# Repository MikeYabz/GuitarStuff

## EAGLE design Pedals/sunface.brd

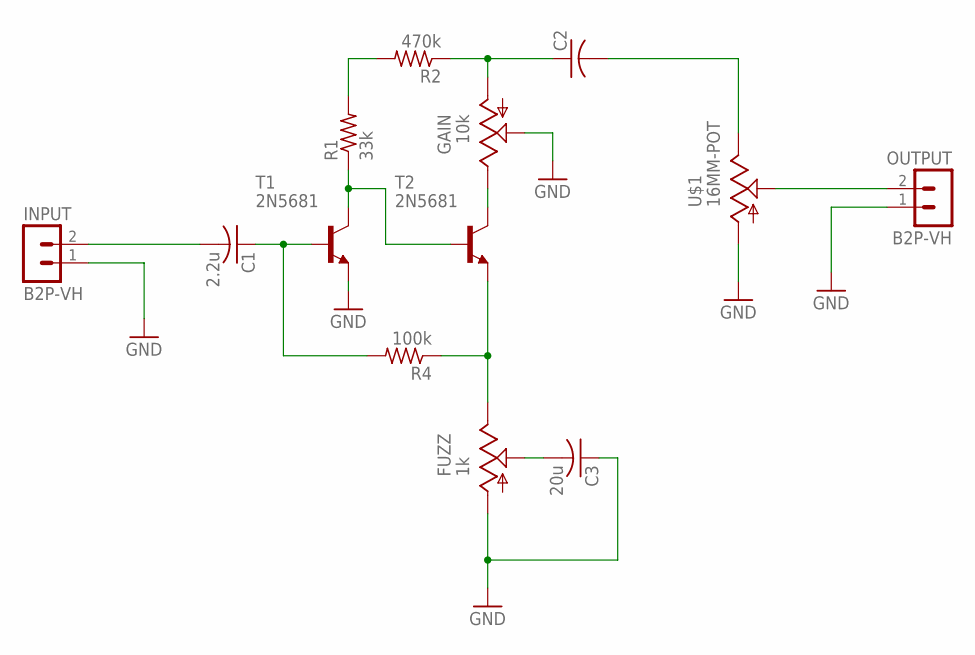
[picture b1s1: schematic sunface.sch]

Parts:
C1: 2.2u; C050-045X075
C2: C-US050-045X075; C050-045X075
C3: 20u; C050-045X075
FUZZ: 1k; ALPHA-16-MINI
GAIN: 10k; ALPHA-16-MINI
INPUT: B2P-VH
OUTPUT: B2P-VH
R1: 33k; 0411/15
R2: 470k; 0411/15
R4: 100k; 0411/15
T1, T2: 2N5681; TO5
U$1: 16MM-POT; ALPHA-16-MINI

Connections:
GND: C3.1, FUZZ.LEFT, GAIN.WIPER, INPUT.1, OUTPUT.1, T1.1 (E), U$1.LEFT
unnamed: R1.1, T1.3 (C), T2.2 (B)
unnamed: C1.1, R4.2, T1.2 (B)
unnamed: R1.2, R2.2
unnamed: C2.1, GAIN.LEFT, R2.1
unnamed: GAIN.RIGHT, T2.3 (C)
unnamed: FUZZ.RIGHT, R4.1, T2.1 (E)
unnamed: C2.2, U$1.RIGHT
unnamed: OUTPUT.2, U$1.WIPER
unnamed: C1.2, INPUT.2
unnamed: C3.2, FUZZ.WIPER

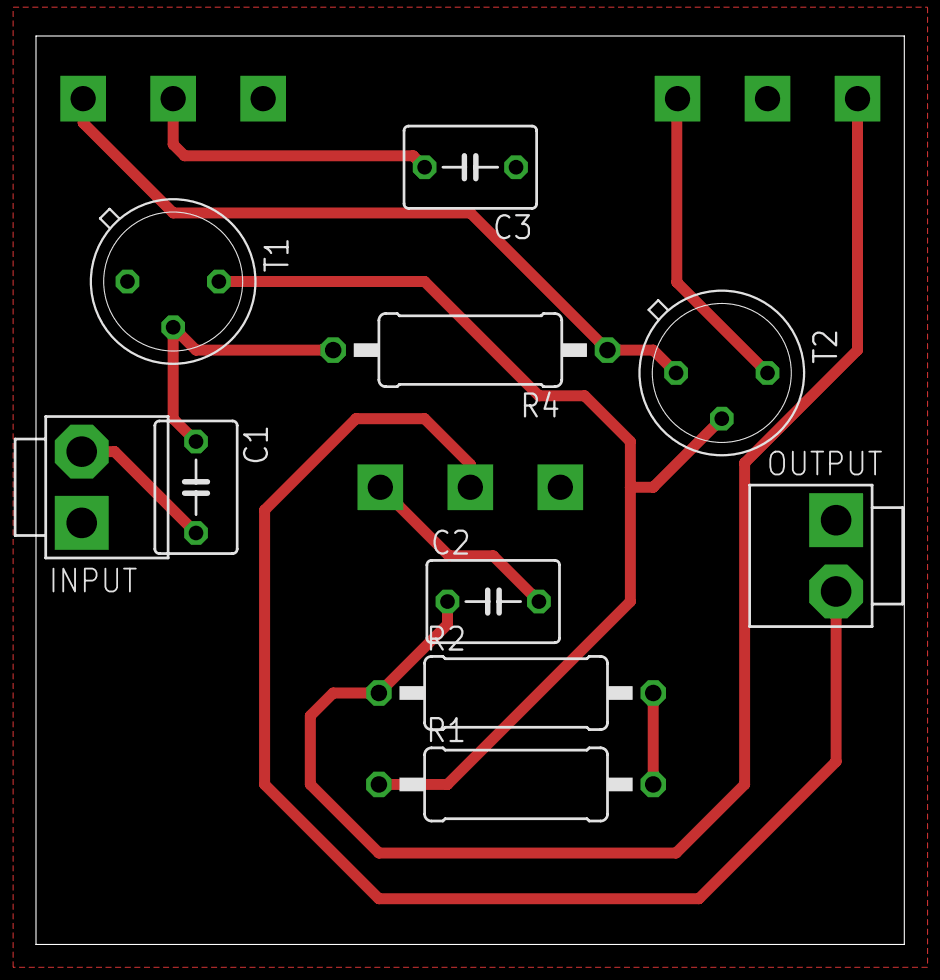
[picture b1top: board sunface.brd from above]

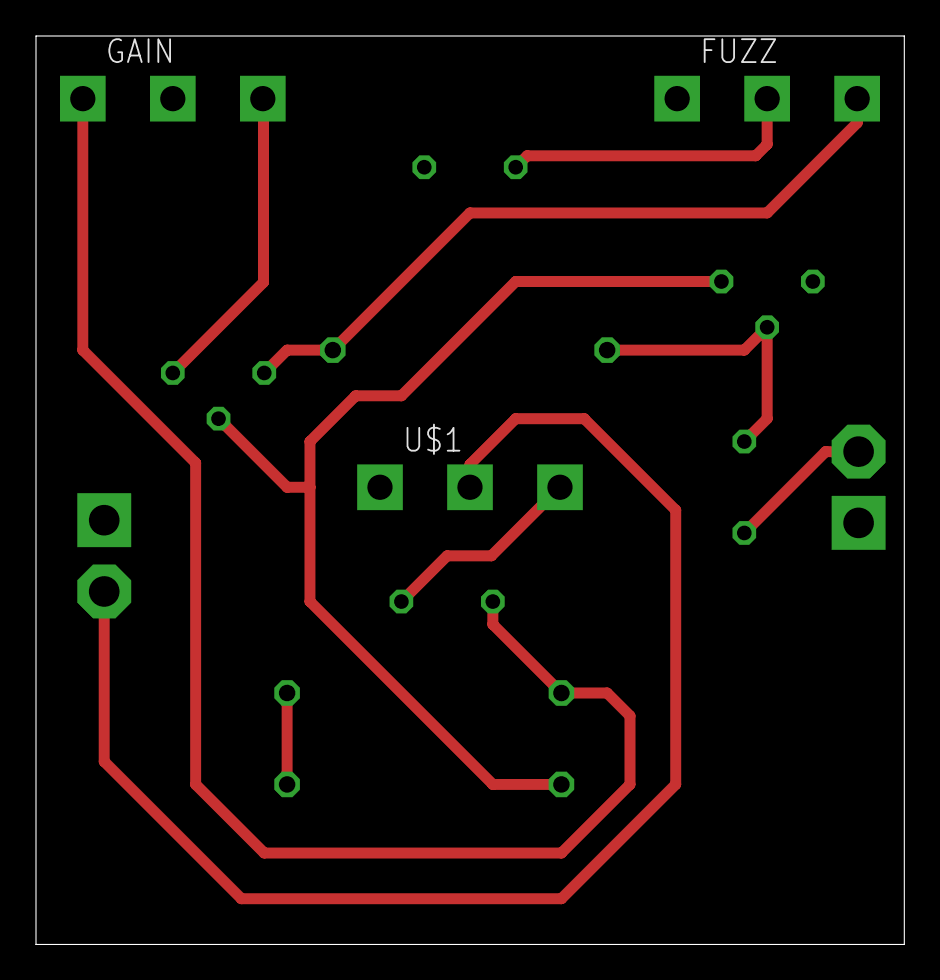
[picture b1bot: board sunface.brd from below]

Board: 2 copper layers, 48.2 x 50.5 mm, 13 parts (3 on the bottom side), 11 nets.

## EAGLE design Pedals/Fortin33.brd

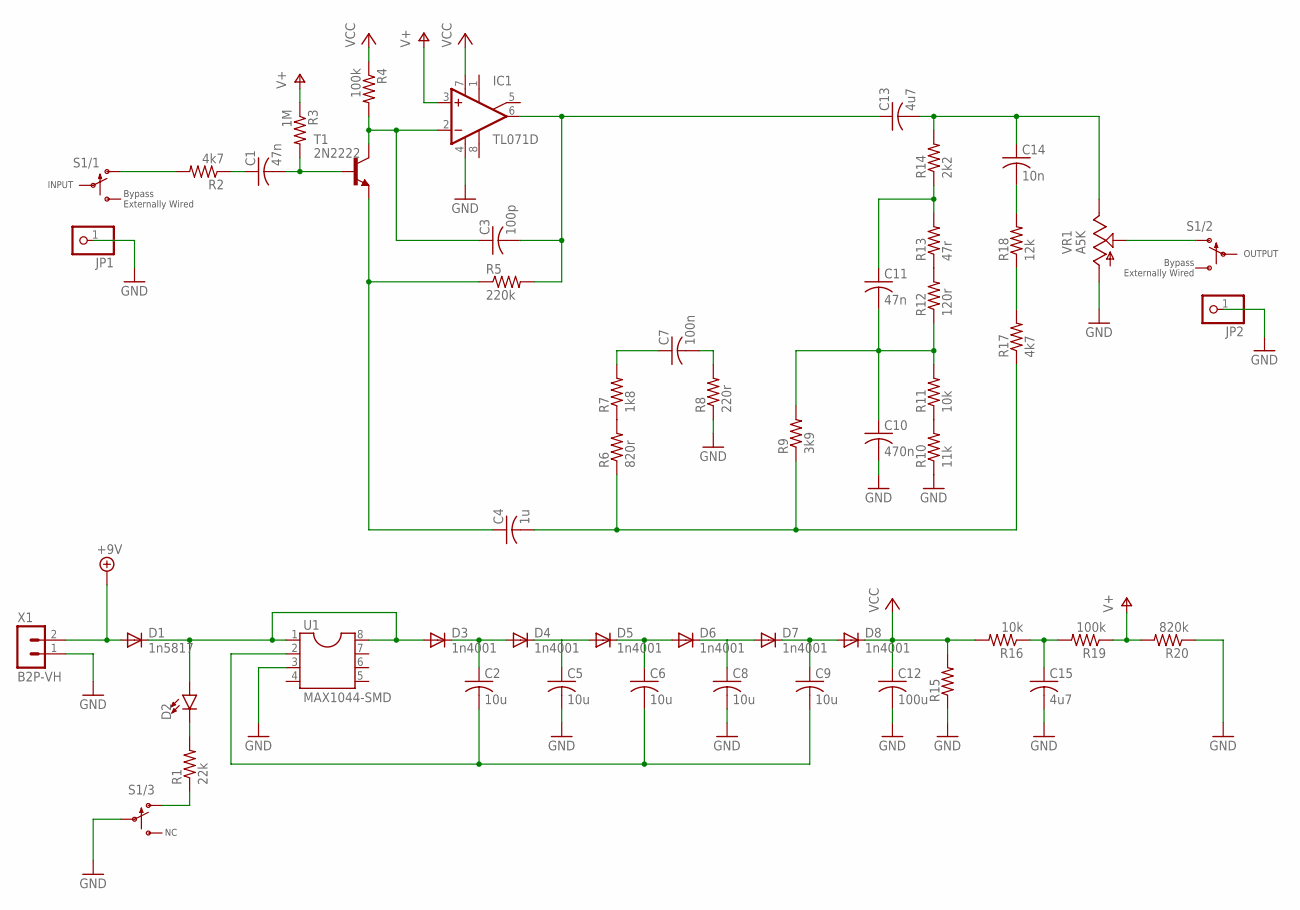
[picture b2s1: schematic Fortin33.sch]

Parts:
C1, C11: 47n; C0603
C2, C5, C6, C8, C9: 10u; C050-025X075
C3: 100p; C0603
C4: 1u; C0603
C7: 100n; C0603
C10: 470n; C0603
C12: 100u; C075-063X106
C13: 4u7; C0603
C14: 10n; C0603
C15: 4u7; C050-025X075
D1: 1n5817; DO41-10
D2: LED3MM; LED_3MM
D3, D4, D5, D6, D7, D8: 1n4001; DO41-10
IC1: TL071D; SO08
JP1, JP2: PINHD-1X1; 1X01
R1: 22k; R0603
R2, R17: 4k7; R0603
R3: 1M; R0603
R4, R19: 100k; R0603
R5: 220k; R0603
R6: 820r; R0603
R7: 1k8; R0603
R8: 220r; R0603
R9: 3k9; R0603
R10: 11k; R0603
R11, R16: 10k; R0603
R12: 120r; R0603
R13: 47r; R0603
R14: 2k2; R0603
R15: R-US_R0603; R0603
R18: 12k; R0603
R20: 820k; R0603
S1: SWITCH-3DPT-INLINE-BREAKOUT-BYPASS; 1X04
T1: 2N2222; TO92-EBC-OVAL
U1: MAX1044-SMD; SO-08
VR1: A5K; ALPHA-16-MINI
X1: B2P-VH

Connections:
+9V: D1.A, X1.2
GND: C5.2, C8.2, C10.2, C12.2, C15.2, IC1.4 (V-), JP1.1, JP2.1, R8.1, R10.1, R15.1, R20.1, S1.3 (COMMON), U1.3, VR1.LEFT, X1.1
unnamed: S1.2 (NORMALLY-ON), VR1.WIPER
unnamed: C1.1, R2.1
unnamed: R2.2, S1.1 (NORMALLY-ON)
unnamed: C3.1, IC1.2 (-IN), R4.2, T1.C
unnamed: C1.2, R3.2, T1.B
unnamed: R12.2, R13.1
unnamed: C3.2, C13.1, IC1.6 (OUT), R5.2
unnamed: C4.1, R5.1, T1.E
unnamed: C11.1, R13.2, R14.1
unnamed: C13.2, C14.1, R14.2, VR1.RIGHT
unnamed: C10.1, C11.2, R9.2, R11.2, R12.1
unnamed: R10.2, R11.1
unnamed: R6.2, R7.1
unnamed: C7.1, R7.2
unnamed: C7.2, R8.2
unnamed: C4.2, R6.1, R9.1, R17.1
unnamed: R17.2, R18.1
unnamed: C14.2, R18.2
unnamed: D1.C, D2.A, D3.A, U1.1, U1.8
unnamed: D2.K (C), R1.2
unnamed: R1.1, S1.4 (NORMALLY-ON)
unnamed: C2.2, C6.2, C9.2, U1.2
unnamed: C2.1, D3.C, D4.A
unnamed: C5.1, D4.C, D5.A
unnamed: C6.1, D5.C, D6.A
unnamed: C8.1, D6.C, D7.A
unnamed: C9.1, D7.C, D8.A
unnamed: C15.1, R16.1, R19.2
V+: IC1.3 (+IN), R3.1, R19.1, R20.2
VCC: C12.1, D8.C, IC1.7 (V+), R4.1, R15.2, R16.2

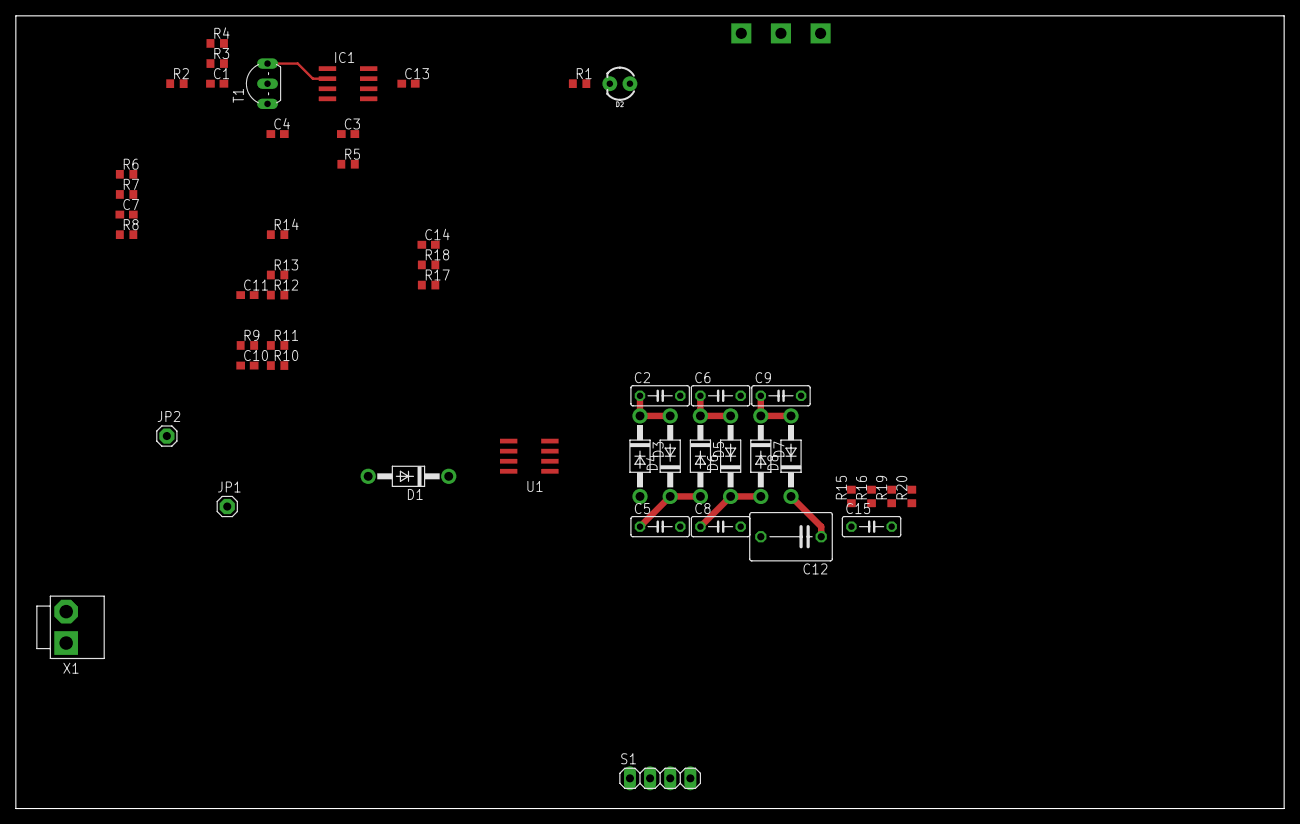
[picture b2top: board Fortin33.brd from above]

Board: 2 copper layers, 160.0 x 100.0 mm, 51 parts (0 on the bottom side), 32 nets.

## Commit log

2020-09-16 initial

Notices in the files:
parts and their libraries:
SparkFun-LED: Licensing: Creative Commons ShareAlike 4.0 International - https://creativecommons.org/licenses/by-sa/4.0
